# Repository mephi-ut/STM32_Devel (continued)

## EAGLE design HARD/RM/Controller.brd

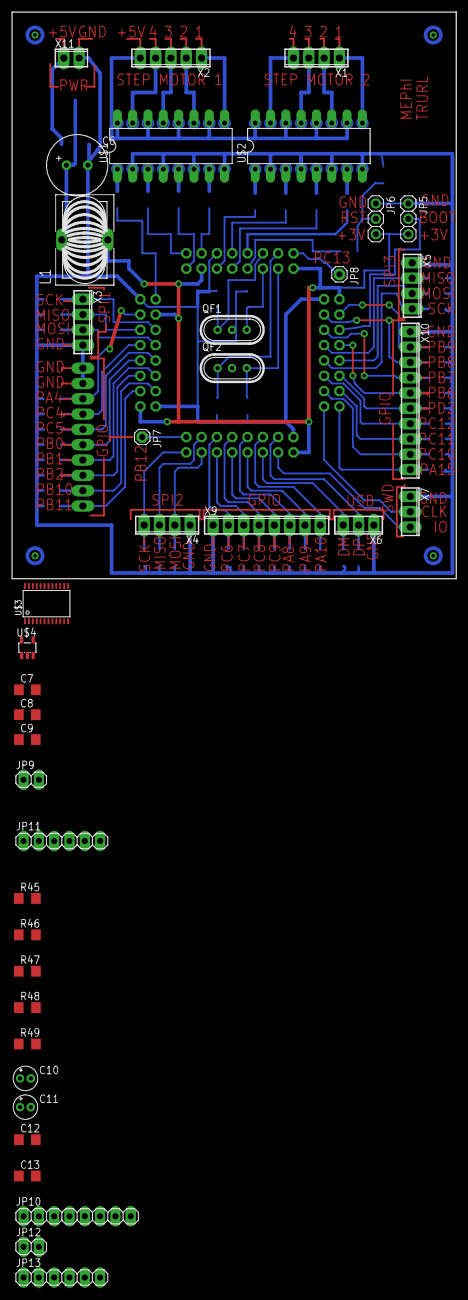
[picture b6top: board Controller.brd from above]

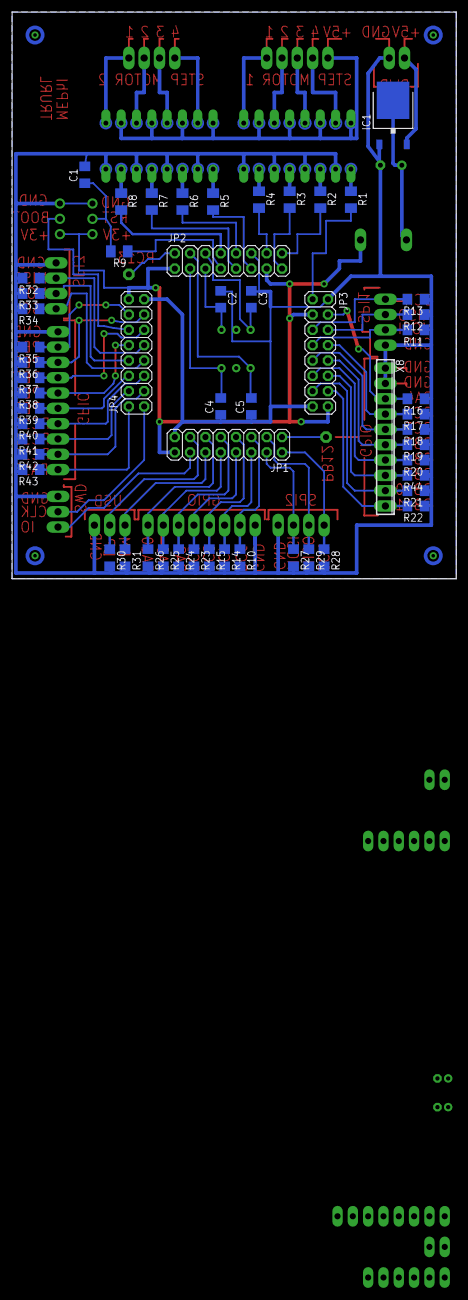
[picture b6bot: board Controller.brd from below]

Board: 2 copper layers, 73.7 x 94.0 mm, 94 parts (55 on the bottom side), 101 nets.

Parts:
C1, C2, C3, C4, C5: C1206
C6: E3,5-10
C7: 1uF; C1206
C8: 2.2uF; C1206
C9: 0.01uF; C1206
C10, C11: 22uF; E1,8-4
C12, C13: 0.1uF; C1206
IC1: LM1117IDTX-5.0; TO252
JP1, JP2, JP3, JP4: 2X08
JP5, JP6: 1X03
JP7, JP8: 1X01
JP9, JP12: 1X02
JP10: 1X08
JP11, JP13: 1X06
L1: A26GFC
QF1, QF2: 8M10AHC49T; HC49U
R1, R2, R3, R4, R5, R6, R7, R8: 100; M1206
R9: M1206
R10, R11, R12, R13, R14, R15, R16, R17, R18, R19, R20, R21, R22, R23, R24, R25, R26, R27, R28, R29, R30, R31, R32, R33, R34, R35, R36, R37, R38, R39, R40, R41, R42, R43, R44, R45, R46, R47, R48, R49: 100; R1206
U$1, U$2: LTV847; DIL16
U$3: AD7190; TSSOP24
U$4: LP2985AIM5-3.3; SOT25
X1, X3, X4, X5: 4POL254
X2: 5POL254
X6, X7: 3POL254
X8, X10: 10POL254
X9: 8POL254
X11: 2POL254

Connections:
BYPASS: C9.1, U$4.4
unnamed: R1.1, U$1.1
unnamed: R2.1, U$1.3
unnamed: C1.1, JP6.2, R9.2
unnamed: R3.1, U$1.5
unnamed: R5.1, U$2.1
unnamed: R6.1, U$2.3
unnamed: R7.1, U$2.5
unnamed: R8.1, U$2.7
unnamed: R4.1, U$1.7
unnamed: C7.1, C11.+, C12.1, JP9.2, U$3.15, U$3.20, U$4.1, U$4.3
unnamed: JP2.9, R7.2
unnamed: JP2.10, R6.2
unnamed: JP2.11, R5.2
unnamed: JP2.14, R4.2
unnamed: JP2.15, R3.2
unnamed: JP1.16, JP2.1, JP2.13, JP3.3, JP3.16, JP4.16, JP5.3, JP6.3, L1.2
unnamed: JP3.1, R1.2
unnamed: C3.2, JP2.6, QF1.1
unnamed: U$1.10, U$1.12, U$1.14, U$1.16, U$2.10, U$2.12, U$2.14, U$2.16, X2.5
unnamed: U$1.15, X2.4
unnamed: U$1.13, X2.3
unnamed: U$1.11, X2.2
unnamed: U$1.9, X2.1
unnamed: U$2.15, X1.4
unnamed: U$2.13, X1.3
unnamed: U$2.11, X1.2
unnamed: U$2.9, X1.1
unnamed: JP4.9, R32.1, X5.2
unnamed: JP4.8, R33.1, X5.3
unnamed: JP4.7, R34.1, X5.4
unnamed: JP1.4, R27.1, X4.2
unnamed: JP1.3, R29.1, X4.3
unnamed: JP1.2, R28.1, X4.4
unnamed: JP3.7, R11.2, X3.3
unnamed: JP3.6, R12.2, X3.2
unnamed: JP3.5, R13.2, X3.1
unnamed: JP4.1, X7.2
unnamed: JP1.14, X7.3
unnamed: JP1.13, R30.1, X6.2
unnamed: JP1.12, R31.1, X6.3
unnamed: JP3.4, R16.2, X8.3
unnamed: JP3.8, R17.2, X8.4
unnamed: JP3.9, R18.2, X8.5
unnamed: JP3.10, R19.2, X8.6
unnamed: JP3.11, R20.2, X8.7
unnamed: JP3.12, R44.2, X8.8
unnamed: JP3.13, R21.2, X8.9
unnamed: JP3.14, R22.2, X8.10
unnamed: JP1.5, R10.1, X9.2
unnamed: JP1.6, R14.1, X9.3
unnamed: JP1.7, R15.1, X9.4
unnamed: JP1.8, R23.1, X9.5
unnamed: JP1.9, R24.1, X9.6
unnamed: JP1.10, R25.1, X9.7
unnamed: JP1.11, R26.1, X9.8
unnamed: JP4.14, R35.1, X10.2
unnamed: JP4.13, R36.1, X10.3
unnamed: JP4.11, R37.1, X10.4
unnamed: JP4.10, R38.1, X10.5
unnamed: JP4.6, R39.1, X10.6
unnamed: JP4.5, R40.1, X10.7
unnamed: JP4.4, R41.1, X10.8
unnamed: JP4.3, R42.1, X10.9
unnamed: JP4.2, R43.1, X10.10
unnamed: JP1.1, JP7.1
unnamed: C1.2, C2.1, C3.1, C4.1, C5.1, C6.-, IC1.1, JP1.15, JP2.12, JP3.2, JP3.15, JP4.15, JP5.1, JP6.1, R10.2, R11.1, R12.1, R13.1, R14.2, R15.2, R16.1, R17.1, R18.1, R19.1, R20.1, R21.1, R22.1, R23.2, R24.2, R25.2, R26.2, R27.2, R28.2, R29.2, R30.2, R31.2, R32.2, R33.2, R34.2, R35.2, R36.2, R37.2, R38.2, R39.2, R40.2, R41.2, R42.2, R43.2, R44.1, U$1.2, U$1.4, U$1.6, U$1.8, U$2.2, U$2.4, U$2.6, U$2.8, X3.4, X4.1, X5.1, X6.1, X7.1, X8.1, X8.2, X9.1, X10.1, X11.2
unnamed: IC1.2, X11.1
unnamed: JP2.7, R9.1
unnamed: JP4.12, JP5.2
unnamed: C2.2, JP2.5, QF1.3
unnamed: C4.2, JP2.3, QF2.3
unnamed: C5.2, JP2.4, QF2.1
unnamed: JP2.2, JP8.1
unnamed: C6.+, IC1.TAB, L1.1
unnamed: JP2.16, R2.2
unnamed: JP10.1, JP10.3, JP10.5, JP10.7, U$3.17
unnamed: JP2.8, R8.2
unnamed: C8.1, C10.+, C13.1, U$3.21, U$4.5
unnamed: JP11.2, R45.2
unnamed: JP11.3, R46.2
unnamed: JP11.4, R47.2
unnamed: JP11.5, R48.2
unnamed: JP11.6, R49.2
unnamed: R45.1, U$3.24
unnamed: R46.1, U$3.23
unnamed: R47.1, U$3.3
unnamed: R48.1, U$3.4
unnamed: R49.1, U$3.22
unnamed: JP10.8, U$3.11
unnamed: JP10.6, U$3.12
unnamed: JP10.4, U$3.13
unnamed: JP10.2, U$3.14
unnamed: C7.2, C8.2, C9.2, C10.-, C11.-, C12.2, C13.2, JP9.1, JP11.1, JP13.1, U$3.16, U$3.18, U$3.19, U$4.2
unnamed: JP12.2, U$3.1
unnamed: JP12.1, U$3.2
unnamed: JP13.6, U$3.5
unnamed: JP13.5, U$3.6
unnamed: JP13.4, U$3.7
unnamed: JP13.3, U$3.8
unnamed: JP13.2, U$3.10

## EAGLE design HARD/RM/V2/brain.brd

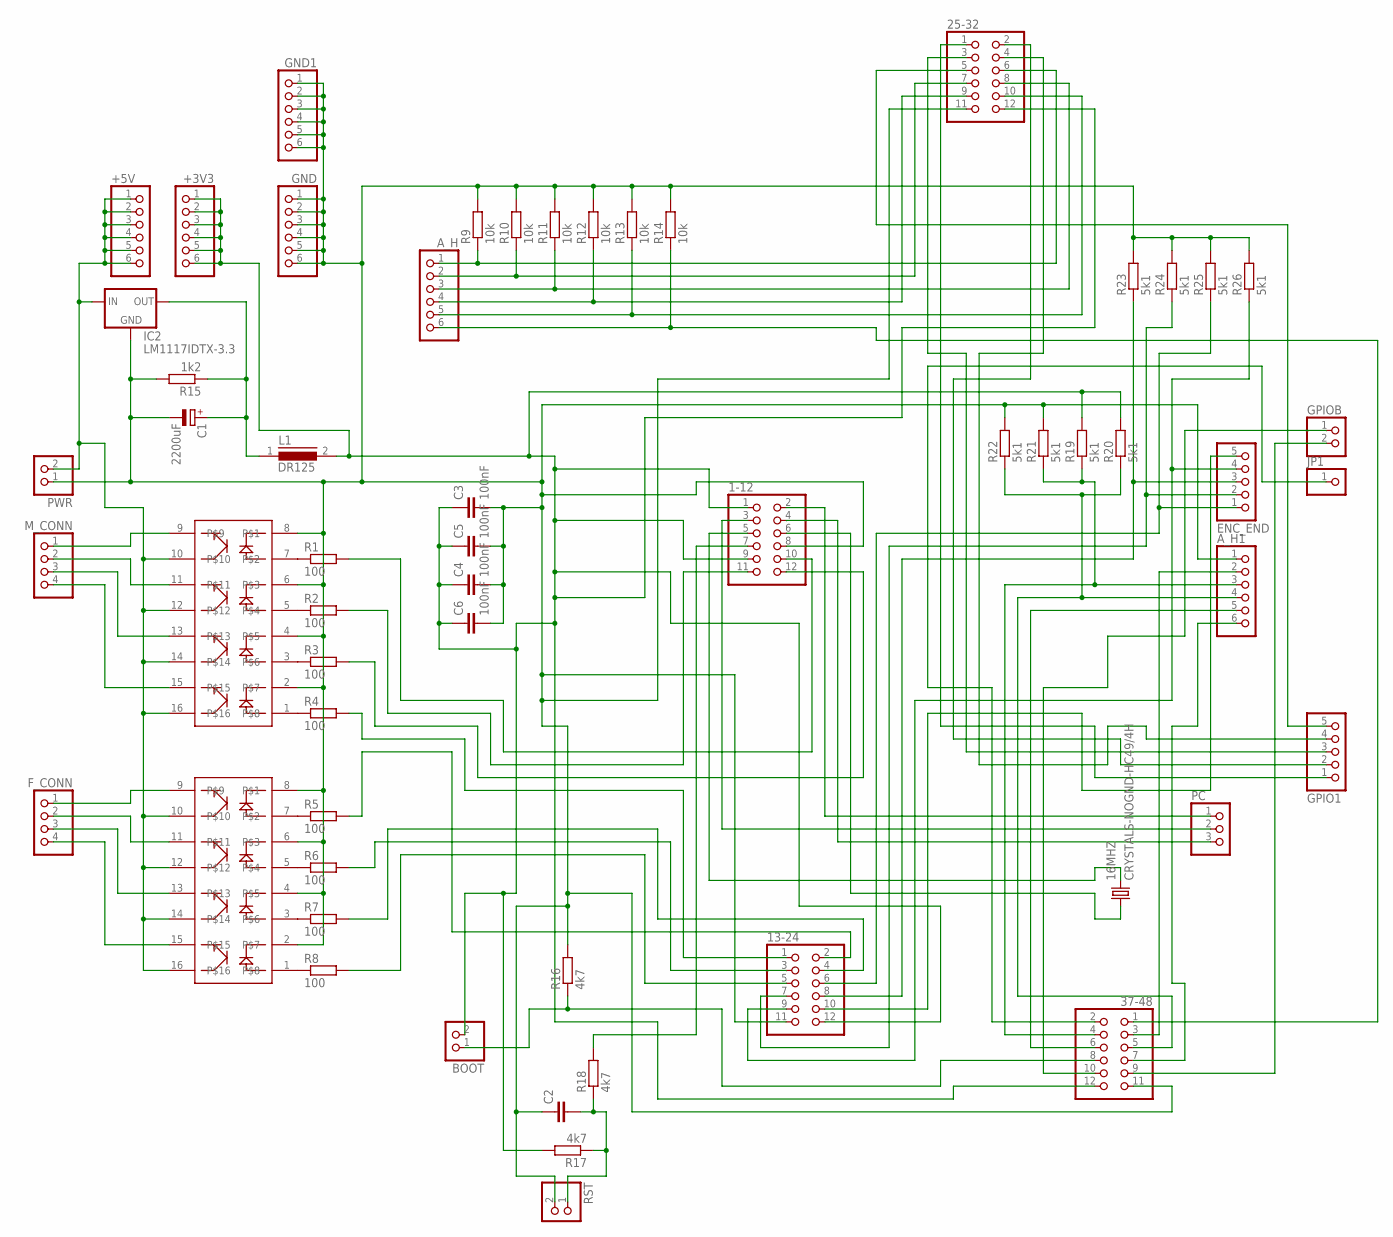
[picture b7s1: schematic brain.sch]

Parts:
1-12, 13-24, 25-32, 37-48: PINHD-2X6; 2X06
16MHZ: CRYSTALS-NOGND-HC49/4H; HC49
+3V3, +5V: PINHD-1X6; 1X06
A_H, A_H1: PINHD-1X6; 1X06
BOOT: PINHD-1X2; 1X02
C1: 2200uF; B45181D
C2: C-EUC1206; C1206
C3, C4, C5, C6: 100nF; C0805
ENC_END: PINHD-1X5; 1X05
F_CONN: PINHD-1X4; 1X04
F_OPTO: LTV847; DIL16
GND, GND1: PINHD-1X6; 1X06
GPIO1: PINHD-1X5; 1X05
GPIOB: PINHD-1X2; 1X02
IC2: LM1117IDTX-3.3; TO252
JP1: PINHD-1X1; 1X01
L1: DR125
M_CONN: PINHD-1X4; 1X04
M_OPTO: LTV847; DIL16
PC: PINHD-1X3; 1X03
PWR: PINHD-1X2; 1X02
R1, R2, R3, R4, R5, R6, R7, R8: 100; R1206
R9, R10, R11, R12, R13, R14: 10k; R1206
R15: 1k2; R1206
R16, R17, R18: 4k7; R1206
R19, R20, R21, R22, R23, R24, R25, R26: 5k1; R1206
RST: PINHD-1X2; 1X02

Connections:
unnamed: 1-12.8, 13-24.11, 25-32.11, 37-48.11, A_H1.1, C1.-, C2.1, C3.2, C4.2, C5.2, C6.2, F_OPTO.2, F_OPTO.4, F_OPTO.6, F_OPTO.8, GND.1, GND.2, GND.3, GND.4, GND.5, GND.6, GND1.1, GND1.2, GND1.3, GND1.4, GND1.5, GND1.6, IC2.1 (GND), M_OPTO.2, M_OPTO.4, M_OPTO.6, M_OPTO.8, PWR.1, R9.2, R10.2, R11.2, R12.2, R13.2, R14.2, R15.2, R16.2, R21.2, R22.2, R23.2, R24.2, R25.2, R26.2, RST.2
unnamed: +5V.1, +5V.2, +5V.3, +5V.4, +5V.5, +5V.6, F_OPTO.10, F_OPTO.12, F_OPTO.14, F_OPTO.16, IC2.2 (IN), M_OPTO.10, M_OPTO.12, M_OPTO.14, M_OPTO.16, PWR.2
unnamed: M_OPTO.7, R1.1
unnamed: M_OPTO.5, R2.1
unnamed: M_OPTO.3, R3.1
unnamed: M_OPTO.1, R4.1
unnamed: F_OPTO.7, R5.1
unnamed: F_OPTO.5, R6.1
unnamed: F_OPTO.3, R7.1
unnamed: F_OPTO.1, R8.1
unnamed: 1-12.10, R1.2
unnamed: 13-24.1, R4.2
unnamed: 37-48.2, JP1.1
unnamed: C2.2, R17.1, R18.1, RST.1
unnamed: 13-24.3, R6.2
unnamed: 13-24.4, R7.2
unnamed: 13-24.5, R8.2
unnamed: M_CONN.1, M_OPTO.9
unnamed: M_CONN.2, M_OPTO.11
unnamed: M_CONN.3, M_OPTO.13
unnamed: M_CONN.4, M_OPTO.15
unnamed: F_CONN.1, F_OPTO.9
unnamed: F_CONN.2, F_OPTO.11
unnamed: F_CONN.3, F_OPTO.13
unnamed: F_CONN.4, F_OPTO.15
unnamed: 25-32.6, A_H.1, R9.1
unnamed: 25-32.7, A_H.2, R10.1
unnamed: 25-32.8, A_H.3, R11.1
unnamed: 25-32.9, A_H.4, R12.1
unnamed: 25-32.10, A_H.5, R13.1
unnamed: 37-48.1, A_H.6, R14.1
unnamed: 1-12.1, 1-12.9, 13-24.12, 25-32.12, 37-48.12, +3V3.1, +3V3.2, +3V3.3, +3V3.4, +3V3.5, +3V3.6, BOOT.2, C3.1, C4.1, C5.1, C6.1, L1.2, R17.2, R19.2, R20.2
unnamed: 1-12.5, 16MHZ.2
unnamed: C1.+, IC2.TAB (OUT), L1.1, R15.1
unnamed: 1-12.6, 16MHZ.1
unnamed: 37-48.8, BOOT.1, R16.1
unnamed: 13-24.6, ENC_END.1, R25.1
unnamed: 1-12.7, R18.2
unnamed: 37-48.7, A_H1.6
unnamed: 37-48.6, A_H1.5
unnamed: 37-48.5, A_H1.4, R20.1, R22.1
unnamed: 13-24.7, ENC_END.2, R24.1
unnamed: 37-48.3, A_H1.2
unnamed: 13-24.8, ENC_END.3, R23.1
unnamed: 37-48.4, A_H1.3, R19.1, R21.1
unnamed: 13-24.9, ENC_END.4, R26.1
unnamed: 1-12.2, PC.1
unnamed: 1-12.3, PC.2
unnamed: 1-12.4, PC.3
unnamed: 13-24.10, ENC_END.5
unnamed: 25-32.1, GPIO1.1
unnamed: 25-32.2, GPIO1.2
unnamed: 25-32.3, GPIO1.3
unnamed: 25-32.4, GPIO1.4
unnamed: 25-32.5, GPIO1.5
unnamed: 37-48.9, GPIOB.2
unnamed: 37-48.10, GPIOB.1
unnamed: 1-12.11, R2.2
unnamed: 1-12.12, R3.2
unnamed: 13-24.2, R5.2

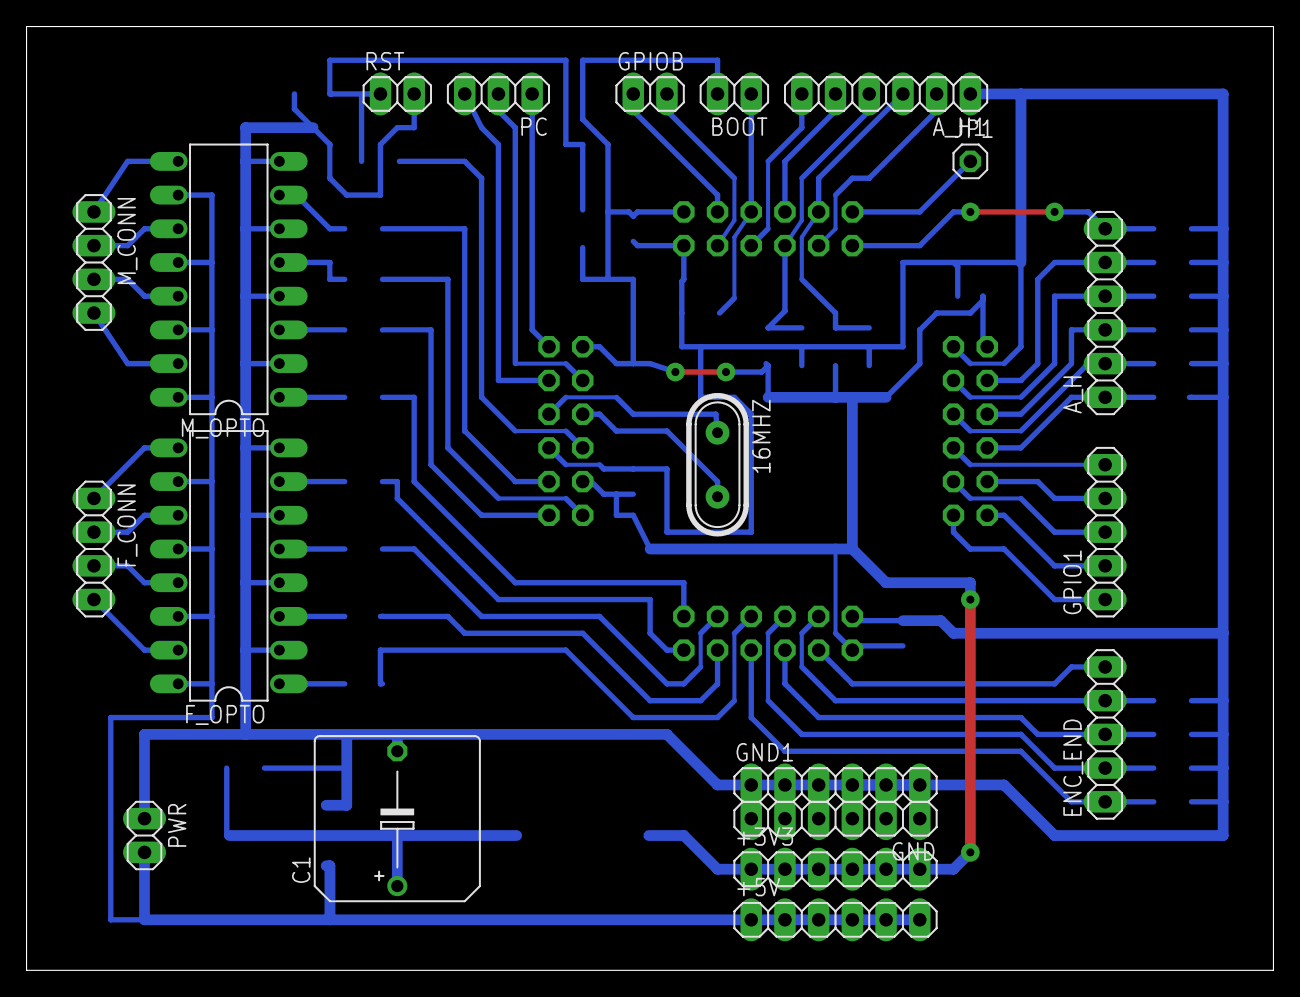
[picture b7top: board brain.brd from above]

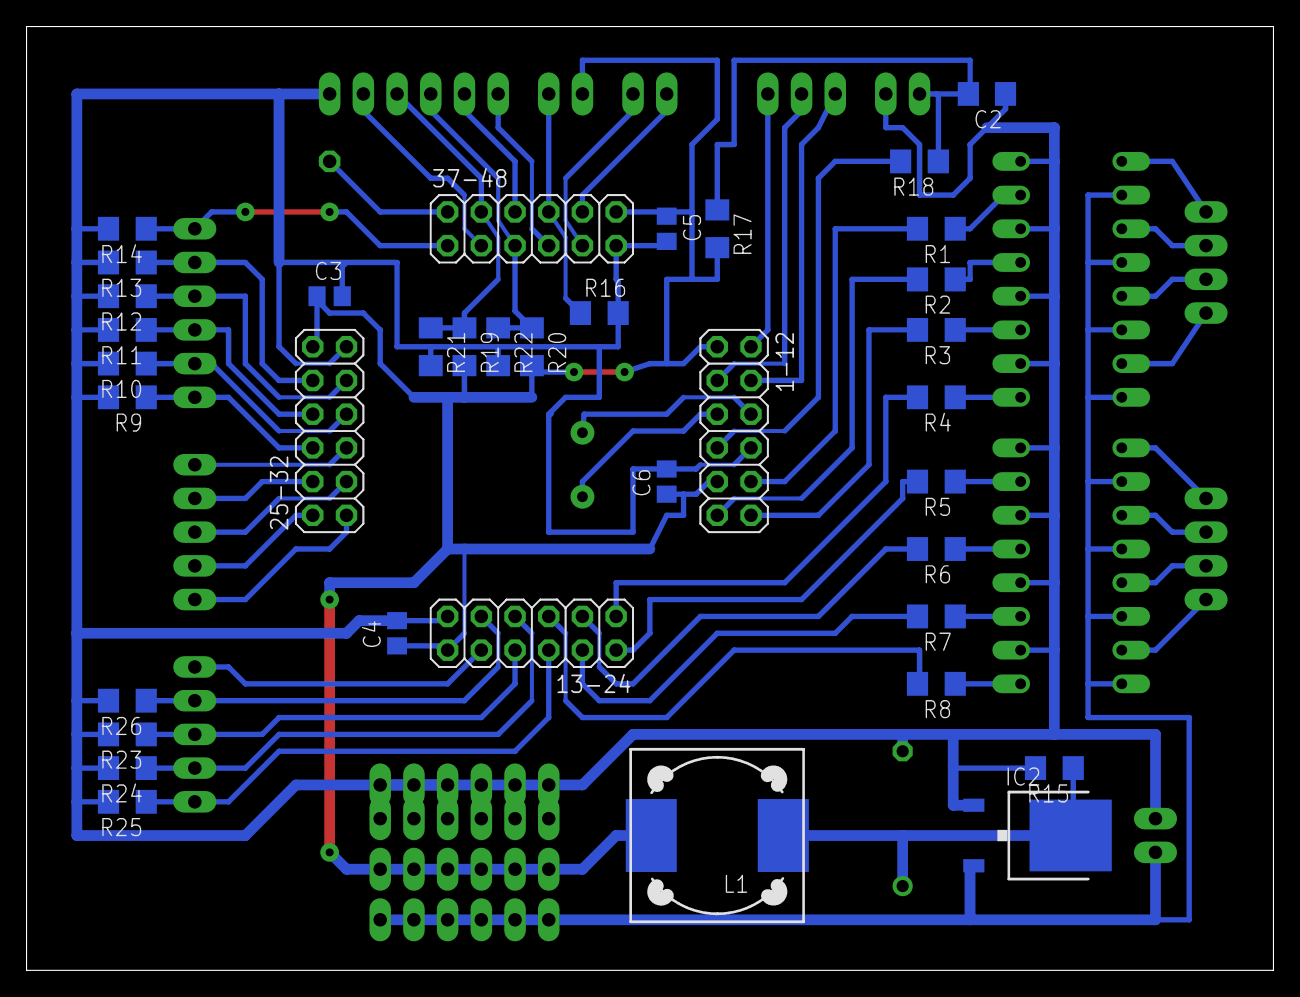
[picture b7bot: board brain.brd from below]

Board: 2 copper layers, 94.0 x 71.1 mm, 57 parts (37 on the bottom side), 60 nets.

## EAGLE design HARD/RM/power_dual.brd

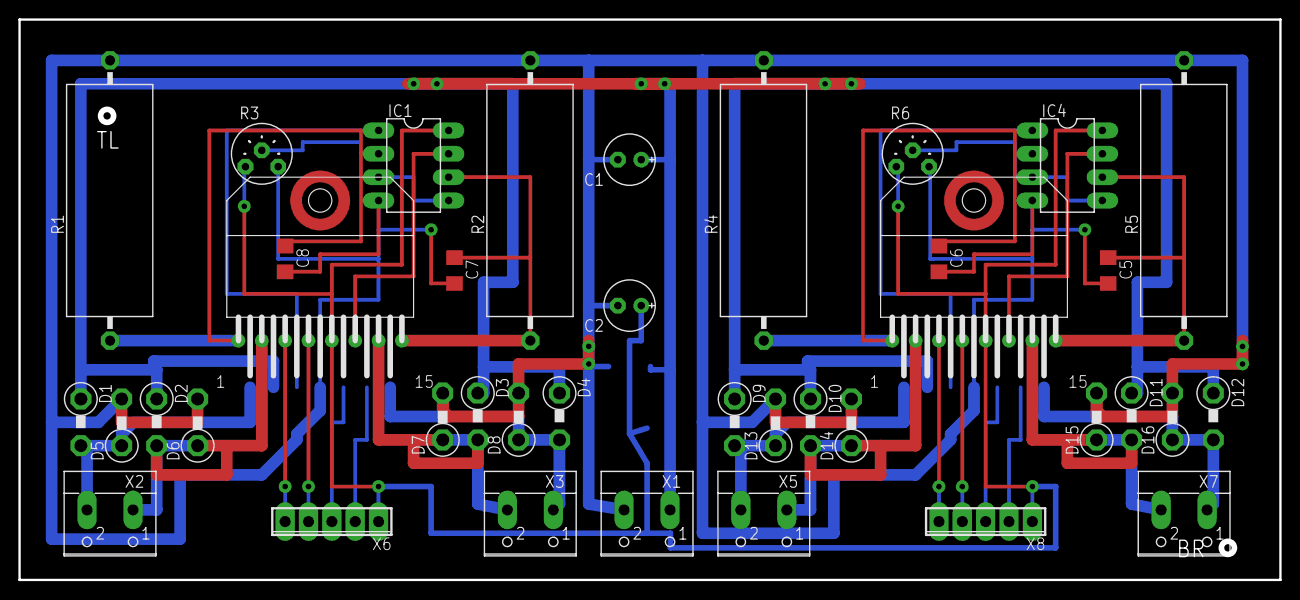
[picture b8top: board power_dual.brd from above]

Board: 2 copper layers, 137.2 x 61.0 mm, 40 parts (1 on the bottom side), 29 nets.

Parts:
C1, C2: E2,5-6E
C5, C6, C7, C8: C1206
D1, D2, D3, D4, D5, D6, D7, D8, D9, D10, D11, D12, D13, D14, D15, D16: C1702-05
IC1, IC4: AD712Q; DIL08
IC3: MC33269D-3.3; DPACK
R1, R2, R4, R5: VTA52
R3, R6: S75H
U$1, U$2: L298-1; MULTIWATT-15-1
X1, X2, X3, X5, X7: W237-102
X6, X8: 5POL254

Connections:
unnamed: C1.-, C2.-, C5.2, C6.2, C7.2, C8.2, D5.A, D6.A, D7.A, D8.A, D13.A, D14.A, D15.A, D16.A, IC1.4, IC3.1, IC4.4, R1.2, R2.2, R3.E, R4.2, R5.2, U$1.P$8, U$2.P$8, X1.2
unnamed: D2.A, D6.C, U$2.P$3, X2.1
unnamed: C2.+, IC1.8, IC3.2, IC4.8, R3.A, R6.A, U$1.P$9, U$2.P$9, X6.1, X8.1
unnamed: C8.1, IC1.2, R1.1, U$2.P$1
unnamed: C7.1, IC1.6, R2.1, U$2.P$15
unnamed: IC1.3, IC1.5, R3.S
unnamed: IC1.1, U$2.P$6
unnamed: IC1.7, U$2.P$11
unnamed: D4.A, D8.C, U$2.P$14, X3.1
unnamed: D3.A, D7.C, U$2.P$13, X3.2
unnamed: D1.A, D5.C, U$2.P$2, X2.2
unnamed: U$2.P$5, X6.5
unnamed: U$2.P$7, X6.4
unnamed: U$2.P$10, X6.3
unnamed: U$2.P$12, X6.2
unnamed: C6.1, IC4.2, R4.1, U$1.P$1
unnamed: C5.1, IC4.6, R5.1, U$1.P$15
unnamed: C1.+, D1.C, D2.C, D3.C, D4.C, D9.C, D10.C, D11.C, D12.C, IC3.3, U$1.P$4, U$2.P$4, X1.1
unnamed: IC4.1, U$1.P$6
unnamed: IC4.7, U$1.P$11
unnamed: D12.A, D16.C, U$1.P$14, X7.1
unnamed: D11.A, D15.C, U$1.P$13, X7.2
unnamed: D10.A, D14.C, U$1.P$3, X5.1
unnamed: D9.A, D13.C, U$1.P$2, X5.2
unnamed: U$1.P$5, X8.5
unnamed: U$1.P$7, X8.4
unnamed: U$1.P$10, X8.3
unnamed: U$1.P$12, X8.2
unnamed: IC4.3, IC4.5, R6.S
